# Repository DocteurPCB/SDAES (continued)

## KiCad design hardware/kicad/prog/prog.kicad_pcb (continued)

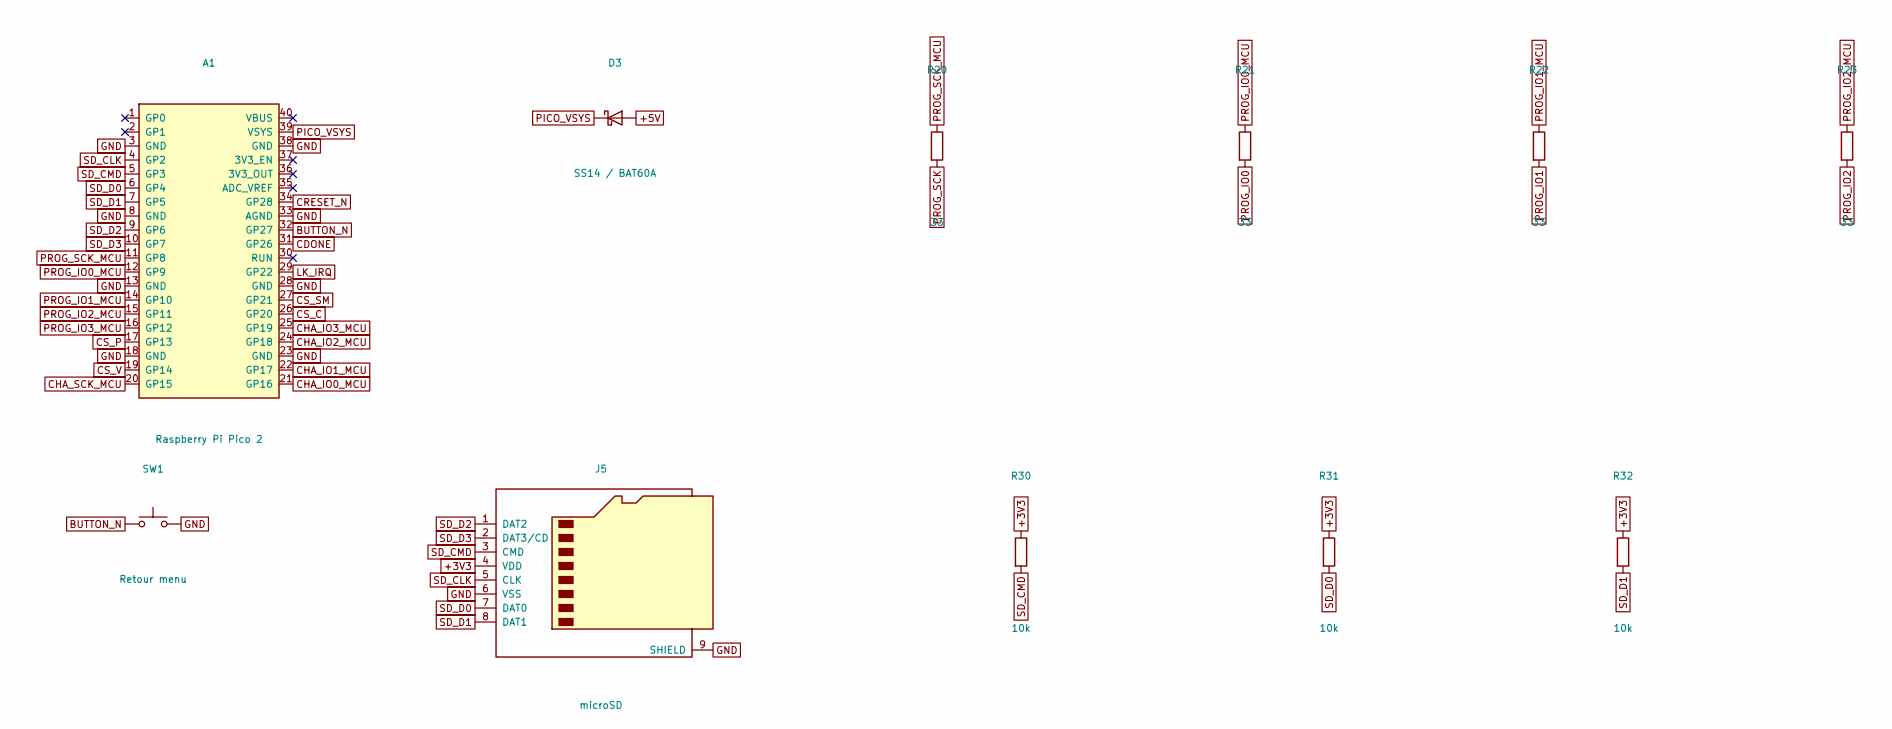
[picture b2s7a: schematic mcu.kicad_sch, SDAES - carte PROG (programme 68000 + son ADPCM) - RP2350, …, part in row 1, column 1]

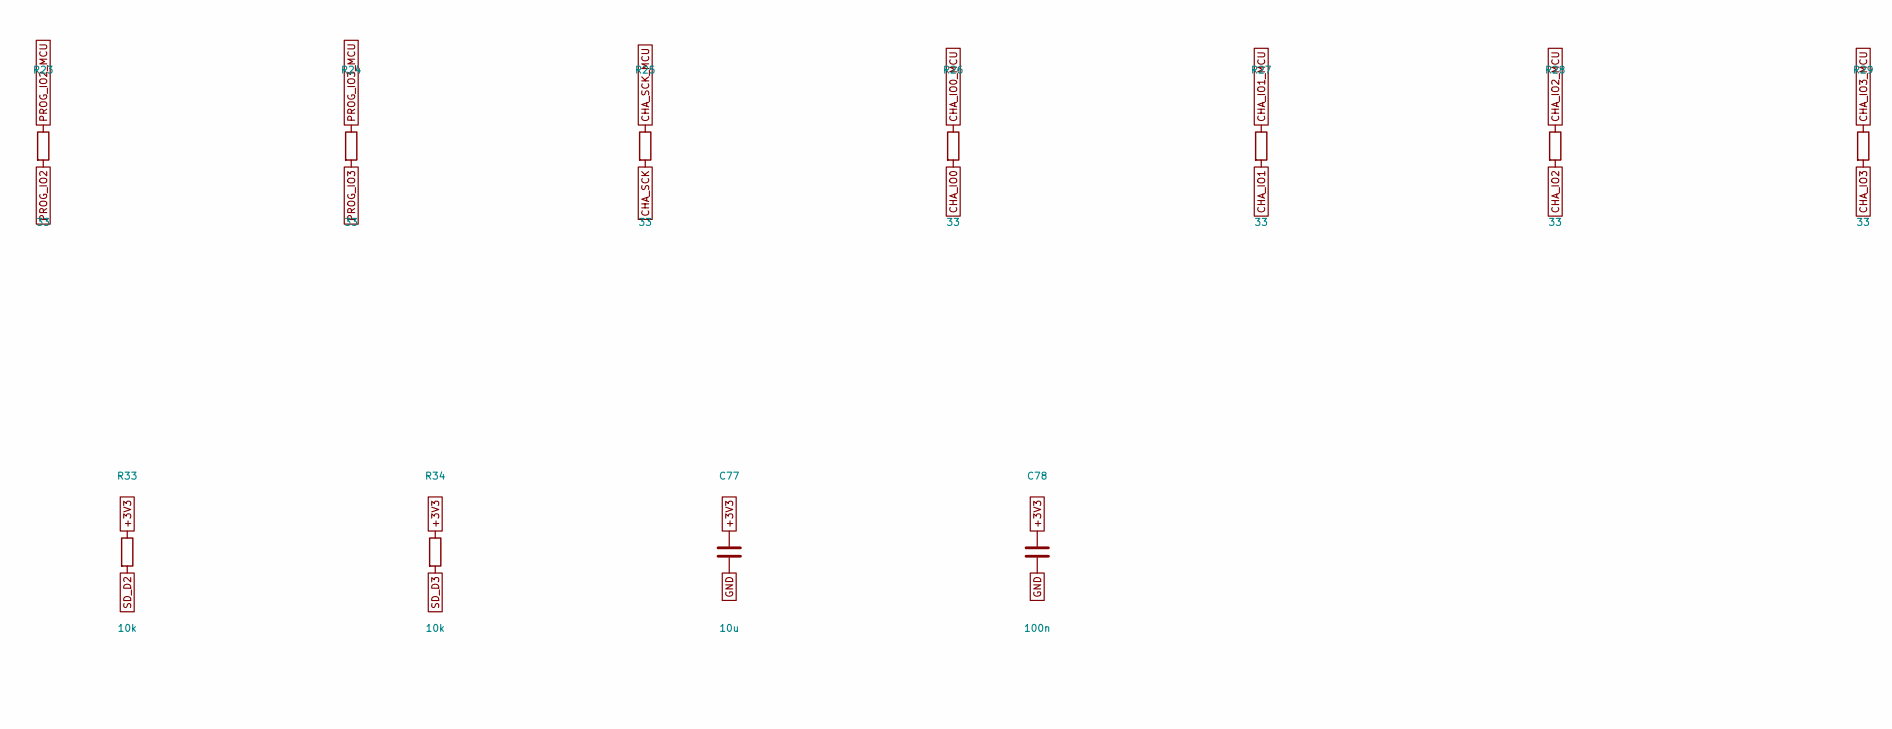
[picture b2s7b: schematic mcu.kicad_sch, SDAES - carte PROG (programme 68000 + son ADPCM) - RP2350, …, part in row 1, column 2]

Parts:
A1: Raspberry Pi Pico 2; RaspberryPi_Pico2_SMD
C77: 10u; C_0805_2012Metric
C78: 100n; C_0603_1608Metric
D3: SS14 / BAT60A; D_SOD-123
J5: microSD; microSD_HC_Wuerth_693072010801
R20, R21, R22, R23, R24, R25, R26, R27, R28, R29: 33; R_0603_1608Metric
R30, R31, R32, R33, R34: 10k; R_0603_1608Metric
SW1: Retour menu; SW_SPST_TL3342

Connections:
+3V3: C77.1, C78.1, J5.4 (VDD), R30.1, R31.1, R32.1, R33.1, R34.1; also elsewhere on the board
+5V: D3.2 (A); also elsewhere on the board
BUTTON_N: A1.32 (GP27), SW1.1
CDONE: A1.31 (GP26); also elsewhere on the board
CHA_IO0: R26.2; also elsewhere on the board
CHA_IO0_MCU: A1.21 (GP16), R26.1
CHA_IO1: R27.2; also elsewhere on the board
CHA_IO1_MCU: A1.22 (GP17), R27.1
CHA_IO2: R28.2; also elsewhere on the board
CHA_IO2_MCU: A1.24 (GP18), R28.1
CHA_IO3: R29.2; also elsewhere on the board
CHA_IO3_MCU: A1.25 (GP19), R29.1
CHA_SCK: R25.2; also elsewhere on the board
CHA_SCK_MCU: A1.20 (GP15), R25.1
CRESET_N: A1.34 (GP28); also elsewhere on the board
CS_C: A1.26 (GP20); also elsewhere on the board
CS_P: A1.17 (GP13); also elsewhere on the board
CS_SM: A1.27 (GP21); also elsewhere on the board
CS_V: A1.19 (GP14); also elsewhere on the board
GND: A1.3 (GND), A1.8 (GND), A1.13 (GND), A1.18 (GND), A1.23 (GND), A1.28 (GND), A1.33 (AGND), A1.38 (GND), C77.2, C78.2, J5.6 (VSS), J5.9 (SHIELD), SW1.2; also elsewhere on the board
LK_IRQ: A1.29 (GP22); also elsewhere on the board
PICO_VSYS: A1.39 (VSYS), D3.1 (K)
PROG_IO0: R21.2; also elsewhere on the board
PROG_IO0_MCU: A1.12 (GP9), R21.1
PROG_IO1: R22.2; also elsewhere on the board
PROG_IO1_MCU: A1.14 (GP10), R22.1
PROG_IO2: R23.2; also elsewhere on the board
PROG_IO2_MCU: A1.15 (GP11), R23.1
PROG_IO3: R24.2; also elsewhere on the board
PROG_IO3_MCU: A1.16 (GP12), R24.1
PROG_SCK: R20.2; also elsewhere on the board
PROG_SCK_MCU: A1.11 (GP8), R20.1
SD_CLK: A1.4 (GP2), J5.5 (CLK)
SD_CMD: A1.5 (GP3), J5.3 (CMD), R30.2
SD_D0: A1.6 (GP4), J5.7 (DAT0), R31.2
SD_D1: A1.7 (GP5), J5.8 (DAT1), R32.2
SD_D2: A1.9 (GP6), J5.1 (DAT2), R33.2
SD_D3: A1.10 (GP7), J5.2 (DAT3/CD), R34.2

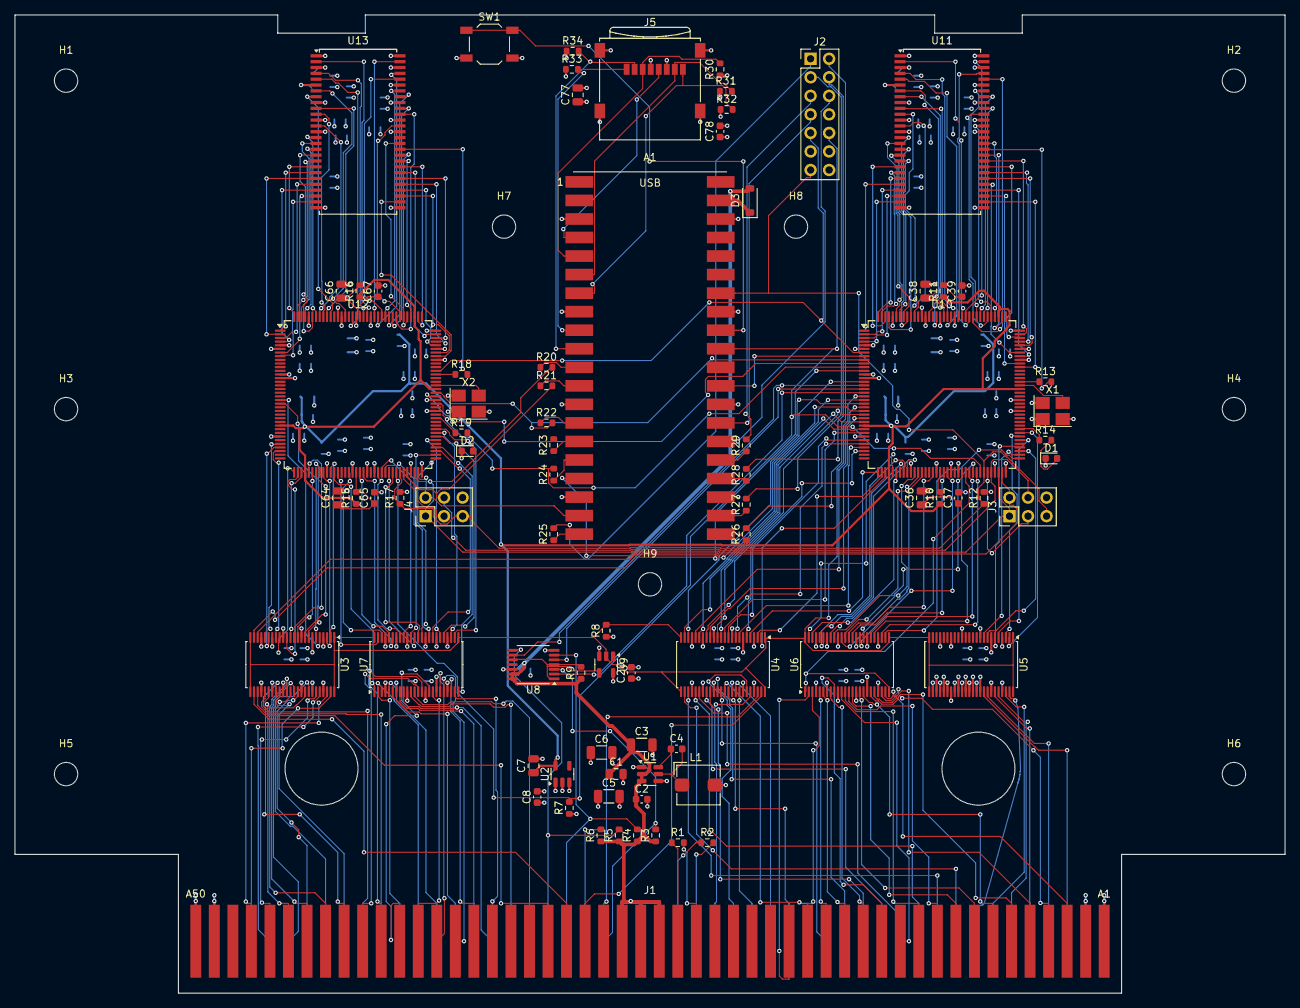
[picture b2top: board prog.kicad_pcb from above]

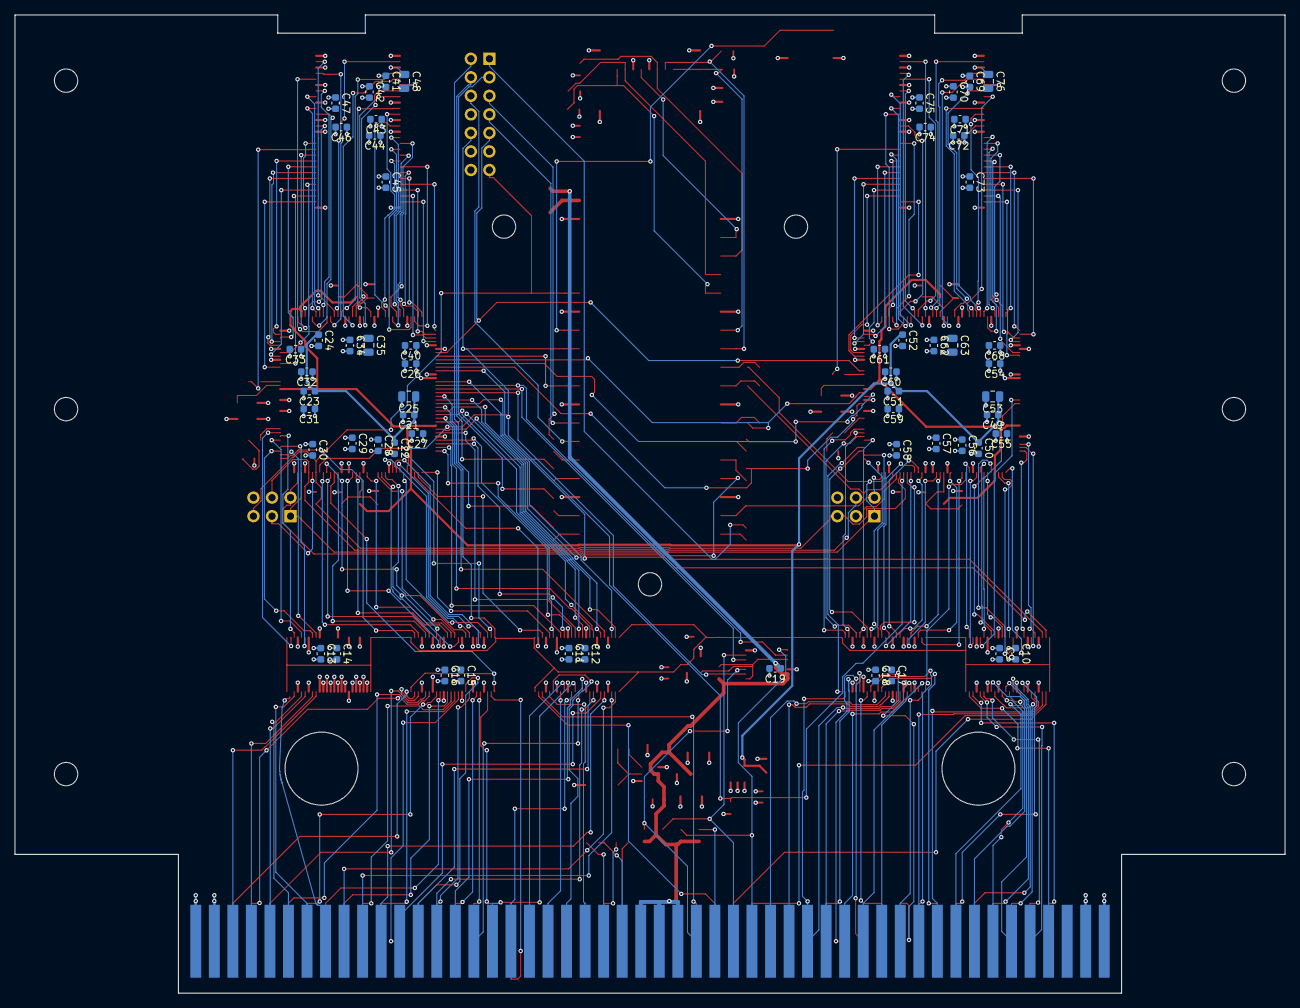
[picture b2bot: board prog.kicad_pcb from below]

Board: 4 copper layers, 174.0 x 134.0 mm, 147 parts (59 on the bottom side), 290 nets.

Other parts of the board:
H1, H2, H3, H4, H5, H6, H7, H8, H9: Entretoise M3; MountingHole_3.2mm_M3

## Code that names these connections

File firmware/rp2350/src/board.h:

/*
 * Affectation des broches du Raspberry Pi Pico 2 (RP2350) sur la carte PROG.
 * Voir docs/04-liaison-rp2350.md et hardware/README.md.
 */
#ifndef SDAES_BOARD_H
#define SDAES_BOARD_H

/* Carte SD en mode SDIO 4 bits (PIO1) : CLK = D0 - 2, D0..D3 consécutifs */
#define PIN_SD_CLK      2
#define PIN_SD_CMD      3
#define PIN_SD_D0       4       /* D1 = 5, D2 = 6, D3 = 7 */

/* Bus de liaison de la carte PROG (FPGA P et V), sur la même carte */
#define PIN_PROG_SCK    8
#define PIN_PROG_IO0    9       /* IO0..IO3 = 9..12 */
#define PIN_CS_P        13
#define PIN_CS_V        14

/* Bus de liaison de la carte CHA (FPGA C et SM), via le câble inter-cartes */
#define PIN_CHA_SCK     15
#define PIN_CHA_IO0     16      /* IO0..IO3 = 16..19 */
#define PIN_CS_C        20
#define PIN_CS_SM       21

#define PIN_PROG_IRQ    22      /* commande du menu en attente (actif haut) */
#define PIN_CDONE       26      /* CDONE des 4 FPGA en ET câblé (drain ouvert) */
#define PIN_BUTTON      27      /* bouton "retour menu" (actif bas) */
#define PIN_CRESET_N    28      /* reset commun des 4 FPGA (tiré à la masse) */
#define PIN_LED         25      /* LED du Pico 2 */

/* Fréquence de la liaison : sys 150 MHz / (2 x LINK_CLKDIV) */
#define LINK_CLKDIV     4.0f    /* 18,75 MHz -> ~9 Mo/s par bus */

#endif

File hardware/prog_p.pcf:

# Contraintes prog_p_top - iCE40HX4K-TQ144 (puce HX8K, outils libres)
# Généré par hardware/gen/fpga_pins.py (ne pas modifier à la main).
# « AES ... » = contact du connecteur de cartouche relié à ce port à
# travers un tampon de niveaux (hardware/aes_connector.csv).
set_io CLK25 93    # input, banc 1, GBIN3
set_io A[1] 74    # input, banc 1, AES PROG dessous 3
set_io A[2] 75    # input, banc 1, AES PROG dessous 4
set_io A[3] 76    # input, banc 1, AES PROG dessous 5
set_io A[4] 78    # input, banc 1, AES PROG dessous 6
set_io A[5] 79    # input, banc 1, AES PROG dessous 7
set_io A[6] 80    # input, banc 1, AES PROG dessous 8
set_io A[7] 20    # input, banc 3, GBIN7, AES PROG dessous 9
set_io A[8] 21    # input, banc 3, GBIN6, AES PROG dessous 10
set_io A[9] 22    # input, banc 3, AES PROG dessous 11
set_io A[10] 23    # input, banc 3, AES PROG dessous 12
set_io A[11] 24    # input, banc 3, AES PROG dessous 13
set_io A[12] 25    # input, banc 3, AES PROG dessous 14
set_io A[13] 26    # input, banc 3, AES PROG dessous 15
set_io A[14] 28    # input, banc 3, AES PROG dessous 16
set_io A[15] 29    # input, banc 3, AES PROG dessous 17
set_io A[16] 31    # input, banc 3, AES PROG dessous 18
set_io A[17] 32    # input, banc 3, AES PROG dessous 19
set_io A[18] 33    # input, banc 3, AES PROG dessous 20
set_io A[19] 34    # input, banc 3, AES PROG dessous 21
set_io D[0] 73    # inout, banc 1, AES PROG dessus 3
set_io D[1] 64    # inout, banc 2, AES PROG dessus 4
set_io D[2] 63    # inout, banc 2, AES PROG dessus 5
set_io D[3] 62    # inout, banc 2, AES PROG dessus 6
set_io D[4] 60    # inout, banc 2, AES PROG dessus 7
set_io D[5] 56    # inout, banc 2, AES PROG dessus 8
set_io D[6] 55    # inout, banc 2, AES PROG dessus 9
set_io D[7] 52    # inout, banc 2, GBIN4, AES PROG dessus 10
set_io D[8] 49    # inout, banc 2, GBIN5, AES PROG dessus 11
set_io D[9] 48    # inout, banc 2, AES PROG dessus 12
set_io D[10] 47    # inout, banc 2, AES PROG dessus 13
set_io D[11] 45    # inout, banc 2, AES PROG dessus 14
set_io D[12] 44    # inout, banc 2, AES PROG dessus 15
set_io D[13] 43    # inout, banc 2, AES PROG dessus 16
set_io D[14] 42    # inout, banc 2, AES PROG dessus 17
set_io D[15] 41    # inout, banc 2, AES PROG dessus 18
set_io ROMOE_N 37    # input, banc 2, AES PROG dessous 22
set_io PORTOEU_N 38    # input, banc 2, AES PROG dessus 28
set_io PORTOEL_N 39    # input, banc 2, AES PROG dessus 29
set_io PORTWEL_N 15    # input, banc 3, AES PROG dessus 31
set_io PORTWEU_N 12    # input, banc 3, AES PROG dessus 30
set_io ROMWAIT_N 18    # output, banc 3, AES PROG dessous 28
set_io PWAIT0_N 17    # output, banc 3, AES PROG dessous 30
set_io PWAIT1_N 16    # output, banc 3, AES PROG dessous 31
set_io XLAT_EN_N 19    # output, banc 3
set_io D_DIR 61    # output, banc 2
set_io LK_SCK 70    # input, configuration SPI
set_io LK_CS_N 71    # input, configuration SPI
set_io LK_IO[0] 68    # inout, configuration SPI
set_io LK_IO[1] 9    # inout, banc 3
set_io LK_IO[2] 10    # inout, banc 3
set_io LK_IO[3] 11    # inout, banc 3
set_io LK_IRQ 8    # output, banc 3
set_io MODE 7    # output, banc 3
set_io SD_CLK 94    # output, banc 1, GBIN2
set_io SD_CKE 110    # output, banc 0
set_io SD_CS_N 141    # output, banc 0
set_io SD_RAS_N 139    # output, banc 0
set_io SD_CAS_N 138    # output, banc 0
set_io SD_WE_N 137    # output, banc 0
set_io SD_BA[0] 142    # output, banc 0
set_io SD_BA[1] 143    # output, banc 0
set_io SD_A[0] 1    # output, banc 3
set_io SD_A[1] 2    # output, banc 3
set_io SD_A[2] 3    # output, banc 3
set_io SD_A[3] 4    # output, banc 3
set_io SD_A[4] 98    # output, banc 1
set_io SD_A[5] 99    # output, banc 1
set_io SD_A[6] 101    # output, banc 1
set_io SD_A[7] 102    # output, banc 1
set_io SD_A[8] 104    # output, banc 1
set_io SD_A[9] 105    # output, banc 1
set_io SD_A[10] 144    # output, banc 0
set_io SD_A[11] 106    # output, banc 1
set_io SD_A[12] 107    # output, banc 1
set_io SD_DQM[0] 136    # output, banc 0
set_io SD_DQM[1] 112    # output, banc 0
set_io SD_DQ[0] 121    # inout, banc 0
set_io SD_DQ[1] 122    # inout, banc 0
set_io SD_DQ[2] 124    # inout, banc 0
set_io SD_DQ[3] 125    # inout, banc 0
set_io SD_DQ[4] 128    # inout, banc 0, GBIN1
set_io SD_DQ[5] 130    # inout, banc 0
set_io SD_DQ[6] 134    # inout, banc 0
set_io SD_DQ[7] 135    # inout, banc 0
set_io SD_DQ[8] 113    # inout, banc 0
set_io SD_DQ[9] 114    # inout, banc 0
set_io SD_DQ[10] 115    # inout, banc 0
set_io SD_DQ[11] 116    # inout, banc 0
set_io SD_DQ[12] 117    # inout, banc 0
set_io SD_DQ[13] 118    # inout, banc 0
set_io SD_DQ[14] 119    # inout, banc 0
set_io SD_DQ[15] 120    # inout, banc 0
set_io LED 81    # output, banc 1

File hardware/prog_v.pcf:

# Contraintes prog_v_top - iCE40HX4K-TQ144 (puce HX8K, outils libres)
# Généré par hardware/gen/fpga_pins.py (ne pas modifier à la main).
# « AES ... » = contact du connecteur de cartouche relié à ce port à
# travers un tampon de niveaux (hardware/aes_connector.csv).
set_io CLK25 93    # input, banc 1, GBIN3
set_io SDRAD[0] 63    # inout, banc 2, AES PROG dessous 32
set_io SDRAD[1] 62    # inout, banc 2, AES PROG dessous 33
set_io SDRAD[2] 61    # inout, banc 2, AES PROG dessous 34
set_io SDRAD[3] 60    # inout, banc 2, AES PROG dessous 35
set_io SDRAD[4] 56    # inout, banc 2, AES PROG dessous 36
set_io SDRAD[5] 55    # inout, banc 2, AES PROG dessous 37
set_io SDRAD[6] 52    # inout, banc 2, GBIN4, AES PROG dessous 38
set_io SDRAD[7] 49    # inout, banc 2, GBIN5, AES PROG dessous 39
set_io SDRA_L[8] 32    # input, banc 3, AES PROG dessous 40
set_io SDRA_L[9] 33    # input, banc 3, AES PROG dessous 41
set_io SDRA_U[20] 37    # input, banc 2, AES PROG dessous 42
set_io SDRA_U[21] 39    # input, banc 2, AES PROG dessous 43
set_io SDRA_U[22] 42    # input, banc 2, AES PROG dessous 44
set_io SDRA_U[23] 44    # input, banc 2, AES PROG dessous 45
set_io SDRMPX 20    # input, banc 3, GBIN7, AES PROG dessous 46
set_io SDROE_N 47    # input, banc 2, AES PROG dessous 47
set_io SDPAD[0] 81    # inout, banc 1, AES PROG dessus 34
set_io SDPAD[1] 80    # inout, banc 1, AES PROG dessus 35
set_io SDPAD[2] 79    # inout, banc 1, AES PROG dessus 36
set_io SDPAD[3] 78    # inout, banc 1, AES PROG dessus 37
set_io SDPAD[4] 75    # inout, banc 1, AES PROG dessus 38
set_io SDPAD[5] 74    # inout, banc 1, AES PROG dessus 39
set_io SDPAD[6] 73    # inout, banc 1, AES PROG dessus 40
set_io SDPAD[7] 64    # inout, banc 2, AES PROG dessus 41
set_io SDPA[8] 34    # input, banc 3, AES PROG dessus 42
set_io SDPA[9] 38    # input, banc 2, AES PROG dessus 43
set_io SDPA[10] 41    # input, banc 2, AES PROG dessus 44
set_io SDPA[11] 43    # input, banc 2, AES PROG dessus 45
set_io SDPMPX 21    # input, banc 3, GBIN6, AES PROG dessus 46
set_io SDPOE_N 45    # input, banc 2, AES PROG dessus 47
set_io RAD_DIR 48    # output, banc 2
set_io PAD_DIR 76    # output, banc 1
set_io LK_SCK 70    # input, configuration SPI
set_io LK_CS_N 71    # input, configuration SPI
set_io LK_IO[0] 68    # inout, configuration SPI
set_io LK_IO[1] 91    # inout, banc 1
set_io LK_IO[2] 90    # inout, banc 1
set_io LK_IO[3] 88    # inout, banc 1
set_io MODE 97    # input, banc 1
set_io SD_CLK 96    # output, banc 1
set_io SD_CKE 113    # output, banc 0
set_io SD_CS_N 143    # output, banc 0
set_io SD_RAS_N 142    # output, banc 0
set_io SD_CAS_N 141    # output, banc 0
set_io SD_WE_N 139    # output, banc 0
set_io SD_BA[0] 144    # output, banc 0
set_io SD_BA[1] 1    # output, banc 3
set_io SD_A[0] 3    # output, banc 3
set_io SD_A[1] 4    # output, banc 3
set_io SD_A[2] 7    # output, banc 3
set_io SD_A[3] 8    # output, banc 3
set_io SD_A[4] 101    # output, banc 1
set_io SD_A[5] 102    # output, banc 1
set_io SD_A[6] 104    # output, banc 1
set_io SD_A[7] 105    # output, banc 1
set_io SD_A[8] 106    # output, banc 1
set_io SD_A[9] 107    # output, banc 1
set_io SD_A[10] 2    # output, banc 3
set_io SD_A[11] 110    # output, banc 0
set_io SD_A[12] 112    # output, banc 0
set_io SD_DQM[0] 138    # output, banc 0
set_io SD_DQM[1] 114    # output, banc 0
set_io SD_DQ[0] 124    # inout, banc 0
set_io SD_DQ[1] 125    # inout, banc 0
set_io SD_DQ[2] 128    # inout, banc 0, GBIN1
set_io SD_DQ[3] 130    # inout, banc 0
set_io SD_DQ[4] 134    # inout, banc 0
set_io SD_DQ[5] 135    # inout, banc 0
set_io SD_DQ[6] 136    # inout, banc 0
set_io SD_DQ[7] 137    # inout, banc 0
set_io SD_DQ[8] 115    # inout, banc 0
set_io SD_DQ[9] 116    # inout, banc 0
set_io SD_DQ[10] 117    # inout, banc 0
set_io SD_DQ[11] 118    # inout, banc 0
set_io SD_DQ[12] 119    # inout, banc 0
set_io SD_DQ[13] 120    # inout, banc 0
set_io SD_DQ[14] 121    # inout, banc 0
set_io SD_DQ[15] 122    # inout, banc 0
set_io LED 84    # output, banc 1

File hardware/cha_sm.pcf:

# Contraintes cha_sm_top - iCE40HX4K-TQ144 (puce HX8K, outils libres)
# Généré par hardware/gen/fpga_pins.py (ne pas modifier à la main).
# « AES ... » = contact du connecteur de cartouche relié à ce port à
# travers un tampon de niveaux (hardware/aes_connector.csv).
set_io CLK25 93    # input, banc 1, GBIN3
set_io P[0] 102    # input, banc 1, AES CHA dessus 11
set_io P[1] 98    # input, banc 1, AES CHA dessous 11
set_io P[2] 101    # input, banc 1, AES CHA dessus 12
set_io P[3] 95    # input, banc 1, AES CHA dessous 12
set_io P[4] 90    # input, banc 1, AES CHA dessus 13
set_io P[5] 91    # input, banc 1, AES CHA dessous 13
set_io P[6] 85    # input, banc 1, AES CHA dessus 14
set_io P[7] 82    # input, banc 1, AES CHA dessous 14
set_io P[8] 87    # input, banc 1, AES CHA dessus 15
set_io P[9] 83    # input, banc 1, AES CHA dessous 15
set_io P[10] 97    # input, banc 1, AES CHA dessus 16
set_io P[11] 84    # input, banc 1, AES CHA dessous 16
set_io P[12] 99    # input, banc 1, AES CHA dessus 17
set_io P[13] 96    # input, banc 1, AES CHA dessous 17
set_io P[14] 94    # input, banc 1, GBIN2, AES CHA dessus 18
set_io P[15] 88    # input, banc 1, AES CHA dessous 18
set_io PCK2B 20    # input, banc 3, GBIN7, AES CHA dessus 4
set_io S2H1 76    # input, banc 1, AES CHA dessus 6
set_io FIXD[0] 75    # output, banc 1, AES CHA dessous 3
set_io FIXD[1] 74    # output, banc 1, AES CHA dessous 4
set_io FIXD[2] 73    # output, banc 1, AES CHA dessous 5
set_io FIXD[3] 64    # output, banc 2, AES CHA dessous 6
set_io FIXD[4] 63    # output, banc 2, AES CHA dessous 7
set_io FIXD[5] 62    # output, banc 2, AES CHA dessous 8
set_io FIXD[6] 61    # output, banc 2, AES CHA dessous 9
set_io FIXD[7] 60    # output, banc 2, AES CHA dessous 10
set_io SDA[0] 79    # input, banc 1, AES CHA dessus 30
set_io SDA[1] 80    # input, banc 1, AES CHA dessus 31
set_io SDA[2] 33    # input, banc 3, AES CHA dessus 32
set_io SDA[3] 34    # input, banc 3, AES CHA dessus 33
set_io SDA[4] 37    # input, banc 2, AES CHA dessus 34
set_io SDA[5] 38    # input, banc 2, AES CHA dessus 35
set_io SDA[6] 39    # input, banc 2, AES CHA dessus 36
set_io SDA[7] 41    # input, banc 2, AES CHA dessus 37
set_io SDA[8] 42    # input, banc 2, AES CHA dessus 38
set_io SDA[9] 43    # input, banc 2, AES CHA dessus 39
set_io SDA[10] 44    # input, banc 2, AES CHA dessus 40
set_io SDA[11] 45    # input, banc 2, AES CHA dessus 41
set_io SDA[12] 47    # input, banc 2, AES CHA dessus 42
set_io SDA[13] 48    # input, banc 2, AES CHA dessus 43
set_io SDA[14] 49    # input, banc 2, GBIN5, AES CHA dessus 44
set_io SDA[15] 52    # input, banc 2, GBIN4, AES CHA dessus 45
set_io SDMRD_N 55    # input, banc 2, AES CHA dessus 46
set_io SDROM_N 56    # input, banc 2, AES CHA dessus 47
set_io SDRD0_N 78    # input, banc 1, AES CHA dessus 28
set_io SDD[0] 23    # output, banc 3, AES CHA dessous 40
set_io SDD[1] 24    # output, banc 3, AES CHA dessous 41
set_io SDD[2] 25    # output, banc 3, AES CHA dessous 42
set_io SDD[3] 26    # output, banc 3, AES CHA dessous 43
set_io SDD[4] 28    # output, banc 3, AES CHA dessous 44
set_io SDD[5] 29    # output, banc 3, AES CHA dessous 45
set_io SDD[6] 31    # output, banc 3, AES CHA dessous 46
set_io SDD[7] 32    # output, banc 3, AES CHA dessous 47
set_io SDD_OE_N 81    # output, banc 1
set_io LK_SCK 70    # input, configuration SPI
set_io LK_CS_N 71    # input, configuration SPI
set_io LK_IO[0] 68    # inout, configuration SPI
set_io LK_IO[1] 107    # inout, banc 1
set_io LK_IO[2] 106    # inout, banc 1
set_io LK_IO[3] 105    # inout, banc 1
set_io MODE 104    # input, banc 1
set_io SR_A[0] 10    # output, banc 3
set_io SR_A[1] 9    # output, banc 3
set_io SR_A[2] 8    # output, banc 3
set_io SR_A[3] 7    # output, banc 3
set_io SR_A[4] 4    # output, banc 3
set_io SR_A[5] 134    # output, banc 0
set_io SR_A[6] 129    # output, banc 0, GBIN0
set_io SR_A[7] 125    # output, banc 0
set_io SR_A[8] 121    # output, banc 0
set_io SR_A[9] 119    # output, banc 0
set_io SR_A[10] 117    # output, banc 0
set_io SR_A[11] 118    # output, banc 0
set_io SR_A[12] 120    # output, banc 0
set_io SR_A[13] 122    # output, banc 0
set_io SR_A[14] 124    # output, banc 0
set_io SR_A[15] 142    # output, banc 0
set_io SR_A[16] 143    # output, banc 0
set_io SR_A[17] 144    # output, banc 0
set_io SR_A[18] 1    # output, banc 3
set_io SR_A[19] 116    # output, banc 0
set_io SR_D[0] 3    # inout, banc 3
set_io SR_D[1] 2    # inout, banc 3
set_io SR_D[2] 141    # inout, banc 0
set_io SR_D[3] 137    # inout, banc 0
set_io SR_D[4] 128    # inout, banc 0, GBIN1
set_io SR_D[5] 130    # inout, banc 0
set_io SR_D[6] 136    # inout, banc 0
set_io SR_D[7] 138    # inout, banc 0
set_io SR_OE_N 139    # output, banc 0
set_io SR_WE_N 135    # output, banc 0

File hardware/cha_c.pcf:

# Contraintes cha_c_top - iCE40HX4K-TQ144 (puce HX8K, outils libres)
# Généré par hardware/gen/fpga_pins.py (ne pas modifier à la main).
# « AES ... » = contact du connecteur de cartouche relié à ce port à
# travers un tampon de niveaux (hardware/aes_connector.csv).
set_io CLK25 93    # input, banc 1, GBIN3
set_io P[0] 12    # input, banc 3, AES CHA dessus 11
set_io P[1] 15    # input, banc 3, AES CHA dessous 11
set_io P[2] 18    # input, banc 3, AES CHA dessus 12
set_io P[3] 19    # input, banc 3, AES CHA dessous 12
set_io P[4] 7    # input, banc 3, AES CHA dessus 13
set_io P[5] 26    # input, banc 3, AES CHA dessous 13
set_io P[6] 8    # input, banc 3, AES CHA dessus 14
set_io P[7] 10    # input, banc 3, AES CHA dessous 14
set_io P[8] 9    # input, banc 3, AES CHA dessus 15
set_io P[9] 17    # input, banc 3, AES CHA dessous 15
set_io P[10] 11    # input, banc 3, AES CHA dessus 16
set_io P[11] 16    # input, banc 3, AES CHA dessous 16
set_io P[12] 22    # input, banc 3, AES CHA dessus 17
set_io P[13] 23    # input, banc 3, AES CHA dessous 17
set_io P[14] 24    # input, banc 3, AES CHA dessus 18
set_io P[15] 25    # input, banc 3, AES CHA dessous 18
set_io P[16] 45    # input, banc 2, AES CHA dessus 19
set_io P[17] 44    # input, banc 2, AES CHA dessous 19
set_io P[18] 48    # input, banc 2, AES CHA dessus 20
set_io P[19] 47    # input, banc 2, AES CHA dessous 20
set_io P[20] 52    # input, banc 2, GBIN4, AES CHA dessus 21
set_io P[21] 49    # input, banc 2, GBIN5, AES CHA dessous 21
set_io P[22] 56    # input, banc 2, AES CHA dessus 22
set_io P[23] 55    # input, banc 2, AES CHA dessous 22
set_io PCK1B 20    # input, banc 3, GBIN7, AES CHA dessus 3
set_io CA4 43    # input, banc 2, AES CHA dessus 10
set_io CLK_12M 21    # input, banc 3, GBIN6, AES CHA dessus 5
set_io EVEN 60    # input, banc 2, AES CHA dessus 7
set_io LOAD 42    # input, banc 2, AES CHA dessus 9
set_io H 41    # input, banc 2, AES CHA dessus 8
set_io GAD[0] 38    # output, banc 2, AES CHA dessous 32
set_io GAD[1] 37    # output, banc 2, AES CHA dessous 33
set_io GAD[2] 34    # output, banc 3, AES CHA dessous 34
set_io GAD[3] 33    # output, banc 3, AES CHA dessous 35
set_io GBD[0] 32    # output, banc 3, AES CHA dessous 36
set_io GBD[1] 31    # output, banc 3, AES CHA dessous 37
set_io GBD[2] 29    # output, banc 3, AES CHA dessous 38
set_io GBD[3] 28    # output, banc 3, AES CHA dessous 39
set_io DOTA 62    # output, banc 2, AES CHA dessous 30
set_io DOTB 61    # output, banc 2, AES CHA dessous 31
set_io XLAT_EN_N 39    # output, banc 2
set_io LK_SCK 70    # input, configuration SPI
set_io LK_CS_N 71    # input, configuration SPI
set_io LK_IO[0] 68    # inout, configuration SPI
set_io LK_IO[1] 2    # inout, banc 3
set_io LK_IO[2] 1    # inout, banc 3
set_io LK_IO[3] 3    # inout, banc 3
set_io MODE 4    # input, banc 3
set_io SD_CLK 94    # output, banc 1, GBIN2
set_io SD_CKE 105    # output, banc 1
set_io SD_CS_N 136    # output, banc 0
set_io SD_RAS_N 135    # output, banc 0
set_io SD_CAS_N 134    # output, banc 0
set_io SD_WE_N 130    # output, banc 0
set_io SD_BA[0] 137    # output, banc 0
set_io SD_BA[1] 138    # output, banc 0
set_io SD_A[0] 141    # output, banc 0
set_io SD_A[1] 142    # output, banc 0
set_io SD_A[2] 143    # output, banc 0
set_io SD_A[3] 144    # output, banc 0
set_io SD_A[4] 95    # output, banc 1
set_io SD_A[5] 96    # output, banc 1
set_io SD_A[6] 97    # output, banc 1
set_io SD_A[7] 98    # output, banc 1
set_io SD_A[8] 99    # output, banc 1
set_io SD_A[9] 101    # output, banc 1
set_io SD_A[10] 139    # output, banc 0
set_io SD_A[11] 102    # output, banc 1
set_io SD_A[12] 104    # output, banc 1
set_io SD_DQM[0] 129    # output, banc 0, GBIN0
set_io SD_DQM[1] 106    # output, banc 1
set_io SD_DQ[0] 118    # inout, banc 0
set_io SD_DQ[1] 119    # inout, banc 0
set_io SD_DQ[2] 120    # inout, banc 0
set_io SD_DQ[3] 121    # inout, banc 0
set_io SD_DQ[4] 122    # inout, banc 0
set_io SD_DQ[5] 124    # inout, banc 0
set_io SD_DQ[6] 125    # inout, banc 0
set_io SD_DQ[7] 128    # inout, banc 0, GBIN1
set_io SD_DQ[8] 107    # inout, banc 1
set_io SD_DQ[9] 110    # inout, banc 0
set_io SD_DQ[10] 112    # inout, banc 0
set_io SD_DQ[11] 113    # inout, banc 0
set_io SD_DQ[12] 114    # inout, banc 0
set_io SD_DQ[13] 115    # inout, banc 0
set_io SD_DQ[14] 116    # inout, banc 0
set_io SD_DQ[15] 117    # inout, banc 0
set_io LED 81    # output, banc 1

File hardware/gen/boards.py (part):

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        cap(sh, ref, "10u", f"{tag}_{pll}")
        cap(sh, ref, "100n", f"{tag}_{pll}")
    res(sh, ref, "10k", "CRESET_N", "GND")
    if "SD_CLK" in pins:
        # résistance série d'horloge SDRAM : contre la broche du FPGA (adaptation
        # à la source), déclarée ici pour être placée près de lui
        res(sh, ref, "33", f"{tag}_SD_CLK", f"{tag}_SD_CLK_R")
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          26: "CDONE", 27: "BUTTON_N", 28: "CRESET_N"}
    for g, net in gp.items():
        pico[pin_of(PICO, f"GP{g}")] = net
    pico[pin_of(PICO, "VSYS")] = "PICO_VSYS"
    sh.add(k.Part(ref("A"), PICO, "Raspberry Pi Pico 2", FP["pico"], pico))
    # VSYS depuis le 5 V de la console, par une diode Schottky (fiche Pico 2)
    sh.add(k.Part(ref("D"), DSCH, "SS14 / BAT60A", FP["schottky"], {2: "+5V", 1: "PICO_VSYS"}))
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    # bus de données Z80 : 74AHCT244, /OE = SDD_OE_N OU OE5_N
    n244 = {pin_of(X244_8, f"{g}A{i}"): f"SDD{(g - 1) * 4 + i}" for g in (1, 2) for i in range(4)}
    n244.update({pin_of(X244_8, f"{g}Y{i}"): f"AES_SDD{(g - 1) * 4 + i}" for g in (1, 2) for i in range(4)})
    n244.update({pin_of(X244_8, "1OE"): "SDD_OE5_N", pin_of(X244_8, "2OE"): "SDD_OE5_N",
                 pin_of(X244_8, "VCC"): "+5V", pin_of(X244_8, "GND"): "GND"})
    sh.add(k.Part(ref("U"), X244_8, "74AHCT244", FP["tssop20"], n244))
    cap(sh, ref, "100n", "+5V")
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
